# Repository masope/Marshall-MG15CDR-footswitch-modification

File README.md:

# Marshall-MG15CD-footswitch-modification-board

This Repository contains PCB design files from KiCAD and source code for modifying Marshall MG15CDR combo guitar amplifier.

## About

Old combo guitar amplifier; Marshall MG15CD, MG15CDR, MG15DFX has 2 Channel; Clean and OD (Overdrive). The amplifier doesn't have footswitch functionality for Channel, Reverb and etc. unlike it's bigger and pricier counterparts.   
   
To give little more life to this good old amplifier, I've designed add-on modification boards to add channel foot-switching functionality by using ATtiny4 MCU.

## controller-board

The board for channel switching. It is powered from the **_power-board_**.     

After remove the old channel switch, the board can be installed to amplifier using [DW-01-09-T-S-450](https://www.samtec.com/products/dw-01-09-t-s-450) Board Stacking Headers (adjust post height to 10.5mm).

The MCU can be programmed through [DF40B-10DS-0.4V(58)](https://www.hirose.com/en/product/p/CL0684-4038-8-58) Board-to-Board Connector. If you're finding mating connector's adaptor board, look [my other repository](https://github.com/masope/DF40C-10DP-0.4V-adaptor).

After installation, you can switch between Clean and OD channels using both on-board tactile switch or external footswitch (I recommend unlatch-type switch like "FS-5U"). You might can make a 1/4" jack footswitch connecter to rear side of a chassis or connect footswitch directly to a on-board 2-pin connector both using [50375023](https://www.molex.com/en-us/products/part-detail/50375023). 

## power-board

The Dual 15V Power can be tapped-off from the amplifier's main board.

After remove the Z2, Z3 from the amplifier, install this board.

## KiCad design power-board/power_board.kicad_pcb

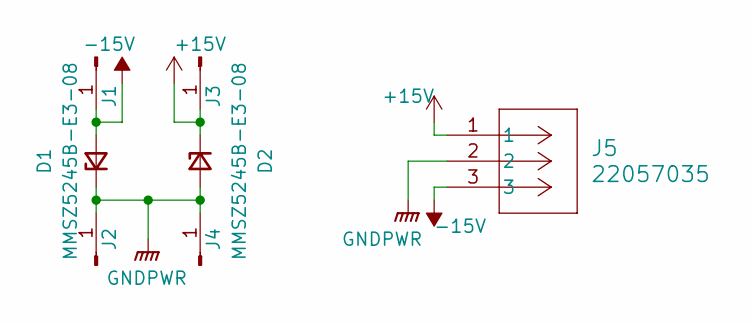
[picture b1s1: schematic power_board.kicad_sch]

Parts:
D1, D2: MMSZ5245B-E3-08; D_SOD-123
J1, J3: Conn_01x01_Pin; PinHeader_1x01_P1.27mm_Vertical
J2, J4: Conn_01x01_Pin
J5: 22057035; CON_22057035_MOL

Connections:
+15V: D2.1 (K), J3.1, J5.1
-15V: D1.2 (A), J1.1, J5.3
GNDPWR: D1.1 (K), D2.2 (A), J2.1, J4.1, J5.2

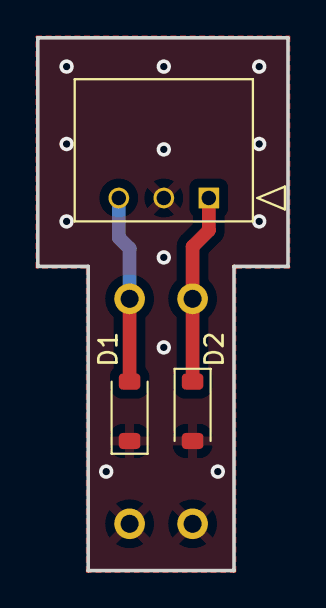
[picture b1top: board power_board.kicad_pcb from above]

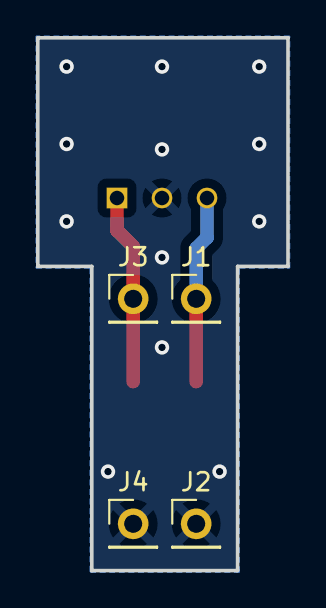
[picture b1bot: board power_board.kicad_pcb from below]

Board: 2 copper layers, 13.9 x 29.6 mm, 7 parts (4 on the bottom side), 3 nets.

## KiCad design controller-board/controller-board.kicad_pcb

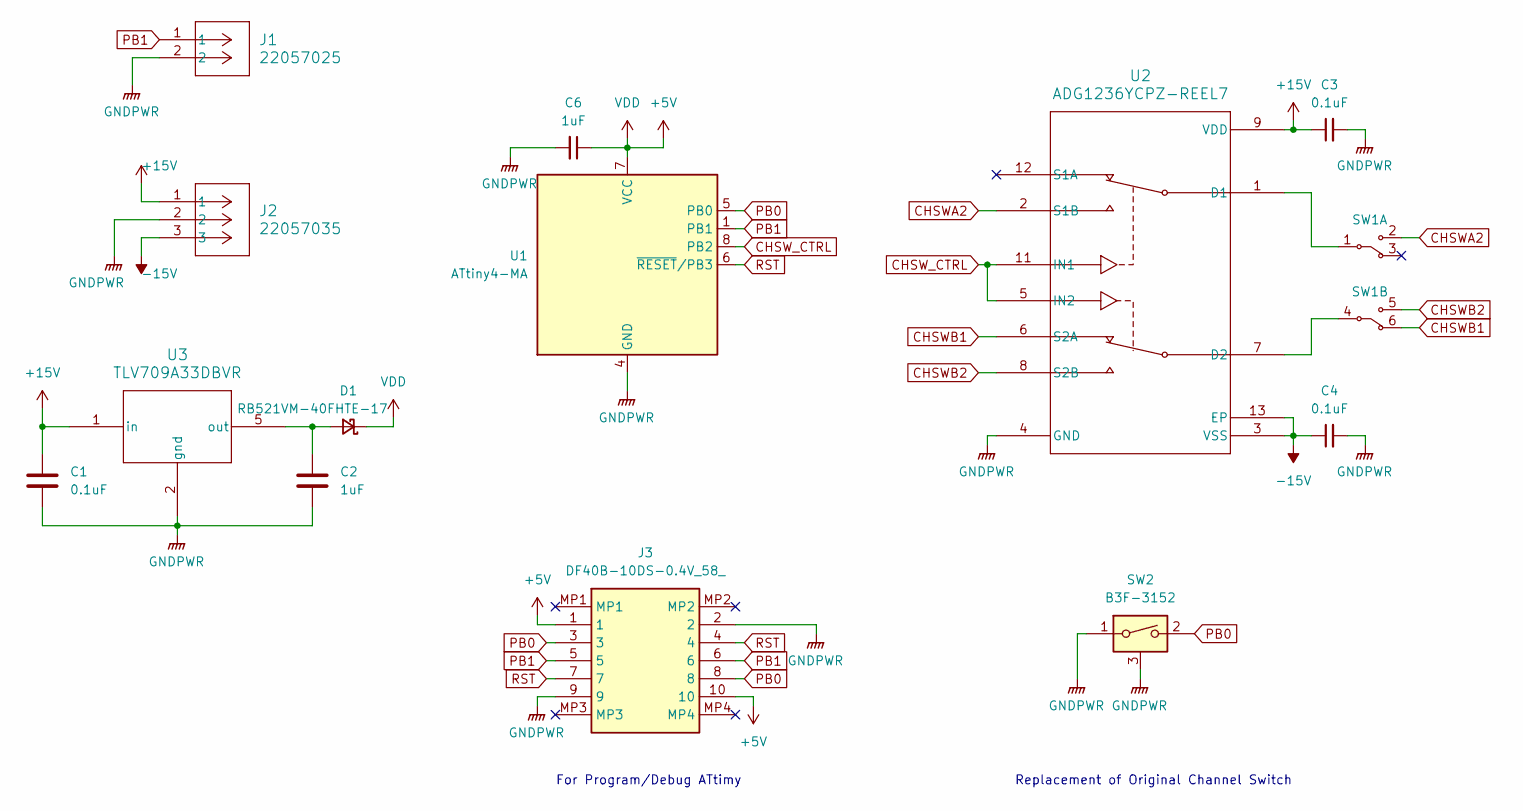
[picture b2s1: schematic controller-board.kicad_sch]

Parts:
C1, C3, C4: 0.1uF; C_0805_2012Metric_Pad1.18x1.45mm_HandSolder
C2, C6: 1uF; C_0805_2012Metric_Pad1.18x1.45mm_HandSolder
D1: RB521VM-40FHTE-17; D_SOD-323_HandSoldering
J1: 22057025; CON_22057025_MOL
J2: 22057035; CON_22057035_MOL
J3: DF40B-10DS-0.4V_58_; DF40B10DS04V58; Mouser Part Number 798-DF40B10DS0.4V58
SW1: Switch_Toggle_Marshall_DPDT
SW2: B3F-3152; B3F3152; Mouser Part Number 653-B3F-3152
U1: ATtiny4-MA; DFN-8-1EP_2x2mm_P0.5mm_EP0.9x1.5mm
U2: ADG1236YCPZ-REEL7; CP_12_1_ADI
U3: TLV709A33DBVR; SOT-23-5_DBV_TEX

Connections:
+5V: C6.1, D1.1 (K), J3.1, J3.10, U1.7 (VCC)
+15V: C1.1, C3.1, J2.1, U2.9 (VDD), U3.1 (in)
-15V: C4.1, J2.3, U2.3 (VSS), U2.13 (EP)
CHSWA2: SW1.2 (A2), U2.2 (S1B)
CHSWB1: SW1.6 (B3), U2.6 (S2A)
CHSWB2: SW1.5 (B2), U2.8 (S2B)
CHSW_CTRL: U1.8 (PB2), U2.5 (IN2), U2.11 (IN1)
GNDPWR: C1.2, C2.2, C3.2, C4.2, C6.2, J1.2, J2.2, J3.2, J3.9, SW2.1, SW2.3, U1.4 (GND), U2.4 (GND), U3.2 (gnd)
unnamed: C2.1, D1.2 (A), U3.5 (out)
unnamed: SW1.1 (A1), U2.1 (D1)
unnamed: SW1.4 (B1), U2.7 (D2)
PB0: J3.3, J3.8, SW2.2, U1.5 (PB0)
PB1: J1.1, J3.5, J3.6, U1.1 (PB1)
RST: J3.4, J3.7, U1.6 (~RESET/PB3)

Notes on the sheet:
For Program/Debug ATtimy
Replacement of Original Channel Switch

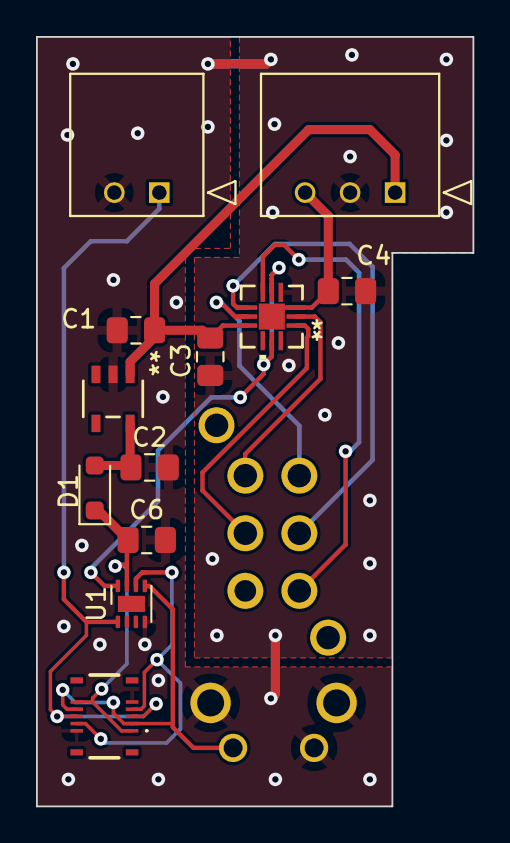
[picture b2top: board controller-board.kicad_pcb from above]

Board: 2 copper layers, 24.2 x 42.8 mm, 14 parts (1 on the bottom side), 14 nets.

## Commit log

2023-10-15 finished fisrt design
2023-10-15 updated README.md & image added
2023-10-15 updated README.md & image relocated
